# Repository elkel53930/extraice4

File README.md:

# ExtraICE4

ExtraICE4 is a competition robot called Micromouse.

For more information on Micromouse competitions, please see the [website](https://www.ntf.or.jp/) of the New Technology Foundation.

## Hardware

- 3DCAD data by Fusion360 : https://t.co/qPmjVBnEnc
  - STL file for 3D printing : under `mecha` directory
- Schematic and PCB design by KiCad7 : under `kicad/extraice` directory

## Firmware

The firmware is written by Rust language.

See [The Rust on ESP Book](https://esp-rs.github.io/book/) for instructions on how to set up the development environment.

The firmware is located under `fsw` directory. This directory is a sub-module, which is actually the micromouse-esp32 repository.

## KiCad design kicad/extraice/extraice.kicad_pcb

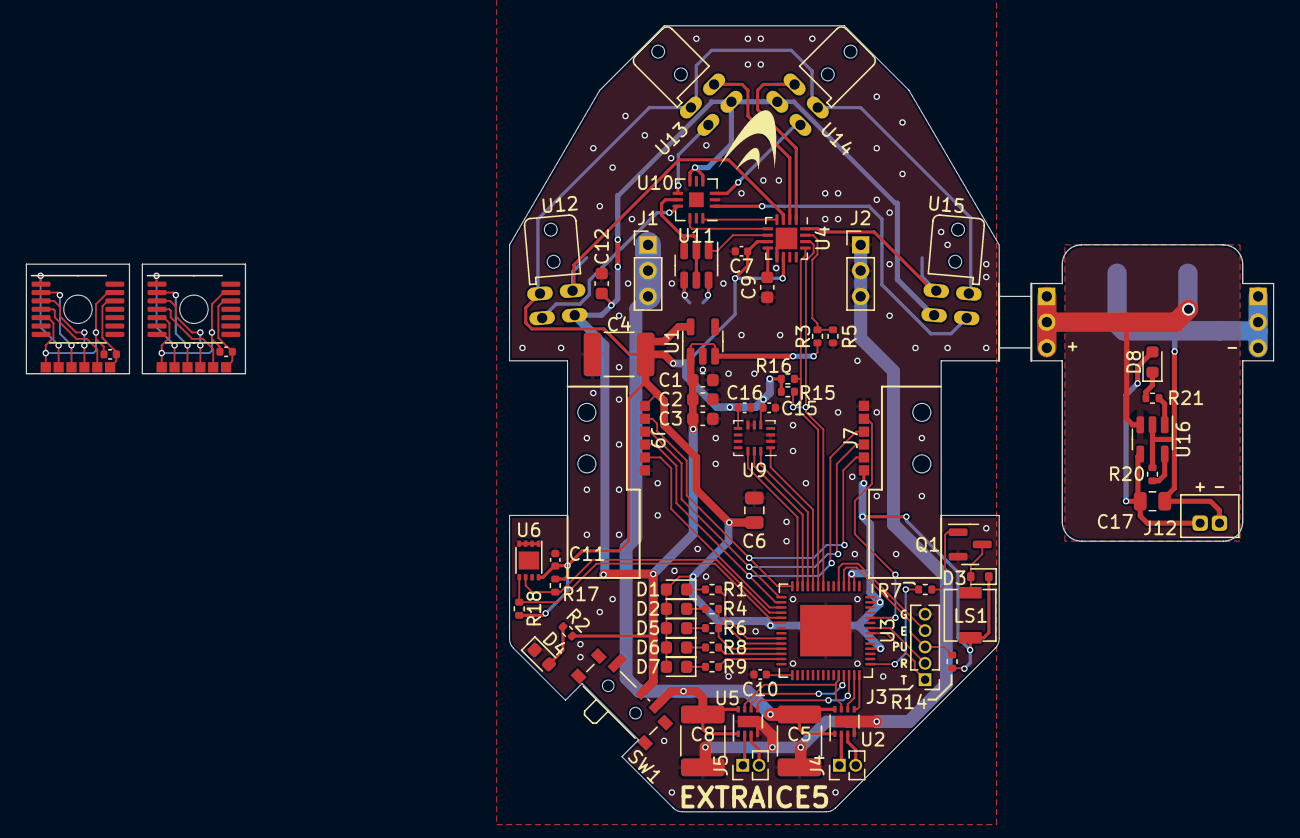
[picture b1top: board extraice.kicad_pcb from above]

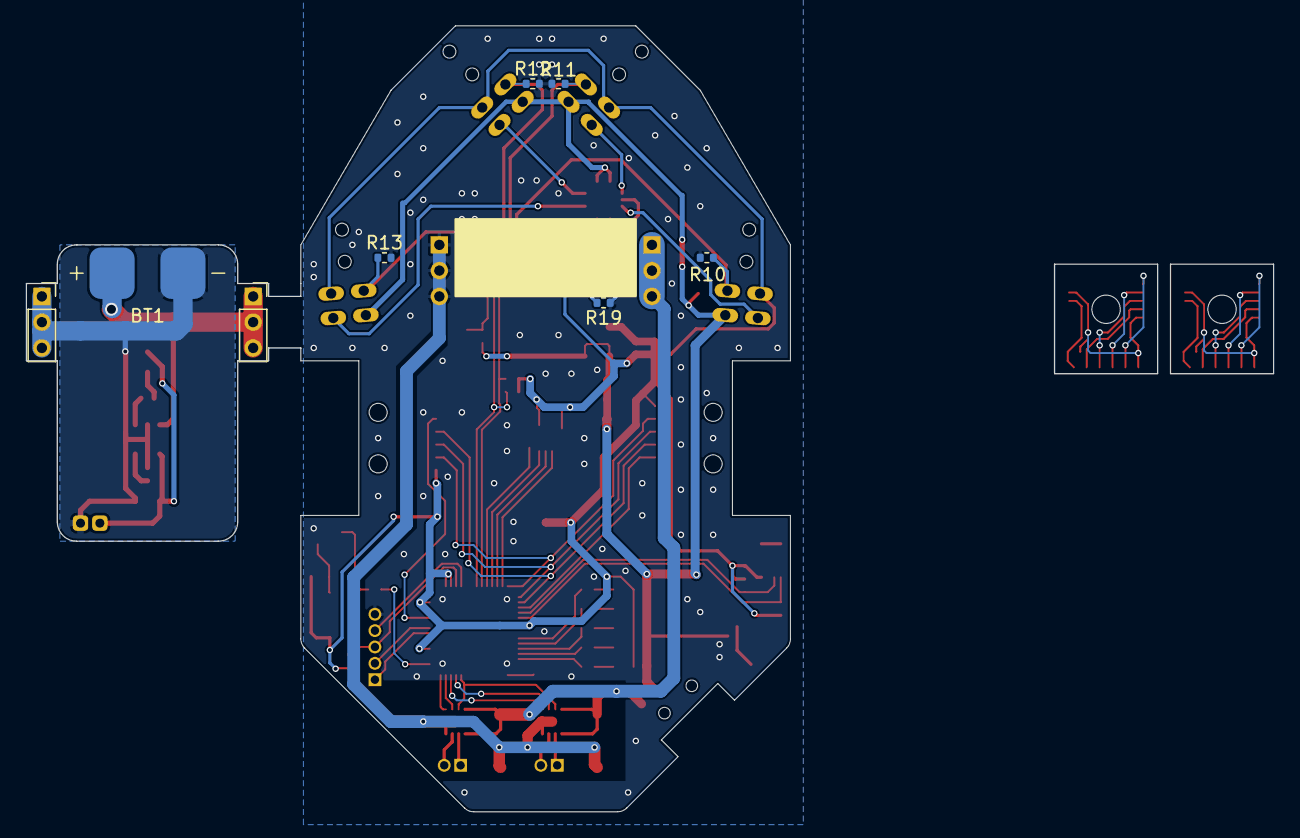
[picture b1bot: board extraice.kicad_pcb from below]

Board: 2 copper layers, 96.8 x 60.9 mm, 84 parts (8 on the bottom side), 78 nets.

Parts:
BT1: 100mAh LiPo; Battery
C1, C2, C3: 1608 10V 4.7uF; C_0603_1608Metric
C4, C5, C8: 4532 10u 16V; C_1812_4532Metric
C6, C17: 2012 35V 10uF; C_0805_2012Metric
C7, C10, C11, C13, C14, C15, C16: 1005 50V 0.1uF; C_0402_1005Metric
C9, C12: 1608 35V 1uF; C_0603_1608Metric
D1, D2, D5, D6, D7, D8: 1608 LED; LED_0603_1608Metric
D3: BAS516; D_SOD-523
D4: 1608 R LED; LED_0603_1608Metric
H1, H2, H3, H4: Φ1.4; Hole1.4
H5, H6: Φ2.2; MountingHole_2.2mm_M2
J1, J2: Conn_01x03; PinHeader_1x03_P2.00mm_Vertical
J3: Conn_01x05; PinHeader_1x05_P1.27mm_Vertical
J4, J5: Conn_01x02; PinHeader_1x02_P1.27mm_Vertical
J6, J8: EncSide; EncoderTerminal
J7, J9: MainSide; EncoderTerminal
J10, J11: Conn_01x03; PinSocket_1x03_P2.00mm_Vertical
J12: Conn_01x02; B2B-ZH
LS1: SMT-0440-T-2-R
Q1: MMBT3904; SOT-23
R1, R4, R6, R8, R9, R15, R16, R17, R18, R21: 1005 1k; R_0402_1005Metric
R2, R3, R5, R14, R20: 1005 10k; R_0402_1005Metric
R7, R10, R11, R12, R13: 1005 470 1%; R_0402_1005Metric
R19: 1005 6.2; R_0402_1005Metric
SW1: PCM12SMTR; SW_SPDT_PCM12
U1: XC6221B302GR; SOT-23-5
U2, U5: DRV8837C; WSON-8-1EP_2x2mm_P0.5mm_EP0.9x1.6mm
U3: ESP32-S3-PICO-1-N8R2; QFN-56-1EP_7x7mm_P0.4mm_EP4x4mm
U4: TLA2528IRTER; WQFN-16-1EP_3x3mm_P0.5mm_EP1.68x1.68mm
U6: MB85RC64TA; LCC-8P-M04
U7, U8: AS5047D; TSSOP-14_4.4x5mm_P0.65mm
U9: LSM6DSR; Bosch_LGA-14_3x2.5mm_P0.5mm
U10: DG2034EDN; QFN-12-1EP_3x3mm_P0.5_EP1.15x1.15
U11: BCR421; SOT-26
U12, U13: PhotoSensorL
U14, U15: PhotoSensorR
U16: LTC4054ES5-4.2; TSOT-23-5

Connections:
+3V0: C4.1, C6.1, C7.1, C11.1, C15.1, C16.1, D1.2 (A), D2.2 (A), D3.1 (K), D5.2 (A), D6.2 (A), D7.2 (A), J7.1, J9.1, LS1.1, R14.2, R15.2, R16.2, R17.2, R18.2, U1.5 (VOUT), U3.2 (VDD3P3), U3.3 (VDD3P3), U3.20 (VDD3P3_RTC), U3.46 (VDD3P3_CPU), U3.55 (VDDA), U3.56 (VDDA), U4.7 (AVDD), U4.10 (DVDD), U6.8 (VDD), U9.5 (Vdd_IO), U9.8 (Vdd), U12.2, U13.2, U14.2, U15.2
+BATT: C1.2, C2.2, C3.2, C12.1, R2.2, R3.2, SW1.2 (B), U1.1 (VIN), U1.3 (CE), U10.4 (EN), U10.6 (V+), U12.3, U13.3, U14.3, U15.3
/BATT_SEN: R3.1, R5.2, U4.15 (AIN0/GPIO0)
/BUZZ: R7.1, U3.43 (GPIO38)
/CHIP_PU: J3.3, R14.1, U3.4 (CHIP_PU)
/CS_ENC_L: J9.5, U3.17 (GPIO12)
/CS_ENC_R: J7.5, U3.52 (GPIO46)
/CS_IMU: U3.13 (GPIO8), U9.12 (CS)
/CWCCW_L: U3.40 (GPIO35), U5.5 (IN2)
/CWCCW_R: U2.5 (IN2), U3.42 (GPIO37)
/GPIO0: J3.4, U3.5 (GPIO0)
/LED_0: R1.2, U3.23 (GPIO17)
/LED_1: R4.2, U3.24 (GPIO18)
/LED_2: R6.2, U3.25 (GPIO19)
/LED_3: R8.2, U3.26 (GPIO20)
/LED_4: R9.2, U3.27 (GPIO21)
/LED_SEL0: U4.4 (AIN5/GPIO5), U10.12 (A0)
/LED_SEL1: U4.5 (AIN6/GPIO6), U10.10 (A1)
/MOT_SLEEP: U2.7 (~SLEEP), U3.38 (GPIO33), U5.7 (~SLEEP)
/PWM_L: U3.39 (GPIO34), U5.6 (IN1)
/PWM_R: U2.6 (IN1), U3.41 (GPIO36)
/RXD: J3.2, U3.50 (U0RXD)
/SCL0: R16.1, U3.9 (GPIO4), U4.13 (SCL)
/SCL1: R18.1, U3.19 (GPIO14), U6.5 (SDA)
/SDA0: R15.1, U3.8 (GPIO3), U4.14 (SDA)
/SDA1: R17.1, U3.18 (GPIO13), U6.6 (SCL)
/SEN_LED_ENA: U4.6 (AIN7/GPIO7), U11.1 (EN)
/SEN_LF: R10.1, U4.3 (AIN4/GPIO4), U12.1
/SEN_LS: R11.1, U4.2 (AIN3/GPIO3), U13.1
/SEN_RF: R13.1, U4.16 (AIN1/GPIO1), U15.1
/SEN_RS: R12.1, U4.1 (AIN2/GPIO2), U14.1
/SPI1_MISO: J7.3, J9.3, U3.15 (GPIO10)
/SPI1_MOSI: J7.2, J9.2, U3.14 (GPIO9)
/SPI1_SCK: J7.4, J9.4, U3.16 (GPIO11)
/SPI2_MISO: U3.10 (GPIO5), U9.1 (SDO/SA0)
/SPI2_MOSI: U3.11 (GPIO6), U9.14 (SDA)
/SPI2_SCK: U3.12 (GPIO7), U9.13 (SCL)
/TXD: J3.1, U3.49 (U0TXD)
/V_MOT: C5.1, C8.1, J1.1, J1.2, J1.3, SW1.3 (C), U2.1 (VM), U2.8 (VCC), U5.1 (VM), U5.8 (VCC)
GND: C1.1, C2.1, C3.1, C4.2, C5.2, C6.2, C7.2, C8.2, C9.1, C10.2, C11.2, C12.2, C15.2, C16.2, D4.1 (K), J2.1, J2.2, J2.3, J3.5, J7.6, J9.6, Q1.2 (E), R5.1, R10.2, R11.2, R12.2, R13.2, R19.1, U1.2 (GND), U2.4 (GND), U2.9 (GND), U3.57 (GND), U4.9 (GND), U4.17 (THPD), U5.4 (GND), U5.9 (GND), U6.1 (A0), U6.2 (A1), U6.3 (A2), U6.4 (VSS), U9.2 (SDx), U9.3 (SCx), U9.6 (GND), U9.7 (GND), U10.2 (GND), U11.4 (GND)
unnamed: BT1.1 (+), J10.1, J10.2, J10.3, U16.3 (BAT)
unnamed: BT1.2 (-), C17.2, J11.1, J11.2, J11.3, J12.1, R20.1, U16.2 (GND)
unnamed: D1.1 (K), R1.1
unnamed: D2.1 (K), R4.1
unnamed: D3.2 (A), LS1.2, Q1.3 (C)
unnamed: D4.2 (A), R2.1
unnamed: D5.1 (K), R6.1
unnamed: D6.1 (K), R8.1
unnamed: D7.1 (K), R9.1
unnamed: C17.1, D8.2 (A), J12.2, U16.4 (V_{CC})
unnamed: D8.1 (K), R21.2
unnamed: J4.1, U2.2 (OUT1)
unnamed: J4.2, U2.3 (OUT2)
unnamed: J5.1, U5.2 (OUT1)
unnamed: J5.2, U5.3 (OUT2)
unnamed: C13.1, J6.1, U7.12 (VDD3V3)
unnamed: J6.2, U7.4 (MOSI)
unnamed: J6.3, U7.3 (MISO)
unnamed: J6.4, U7.2 (CLK)
unnamed: J6.5, U7.1 (~CS)
unnamed: C13.2, J6.6, U7.5 (TST), U7.13 (GND)
unnamed: C14.1, J8.1, U8.12 (VDD3V3)
unnamed: J8.2, U8.4 (MOSI)
unnamed: J8.3, U8.3 (MISO)
unnamed: J8.4, U8.2 (CLK)
unnamed: J8.5, U8.1 (~CS)
unnamed: C14.2, J8.6, U8.5 (TST), U8.13 (GND)
unnamed: Q1.1 (B), R7.2
unnamed: C10.1, U3.29 (VDD_SPI)
unnamed: C9.2, U4.8 (DECAP)
unnamed: U10.8 (COM), U11.2 (OUT), U11.3 (OUT), U11.5 (OUT)
unnamed: U10.1 (S1), U15.4
unnamed: U10.9 (S2), U12.4
unnamed: U10.3 (S3), U14.4
unnamed: U10.7 (S4), U13.4
unnamed: R19.2, U11.6 (Rext)
unnamed: R20.2, U16.5 (PROG)
unnamed: R21.1, U16.1 (~CHRG)

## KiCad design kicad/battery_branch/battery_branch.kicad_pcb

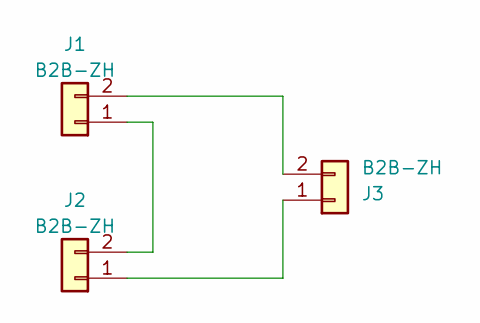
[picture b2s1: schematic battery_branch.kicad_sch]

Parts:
J1, J2, J3: B2B-ZH

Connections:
unnamed: J1.1, J2.2
unnamed: J1.2, J3.2
unnamed: J2.1, J3.1

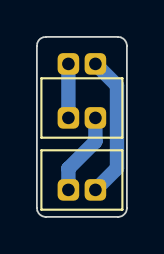
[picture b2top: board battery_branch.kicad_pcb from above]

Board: 2 copper layers, 5.0 x 10.0 mm, 3 parts (1 on the bottom side), 3 nets.

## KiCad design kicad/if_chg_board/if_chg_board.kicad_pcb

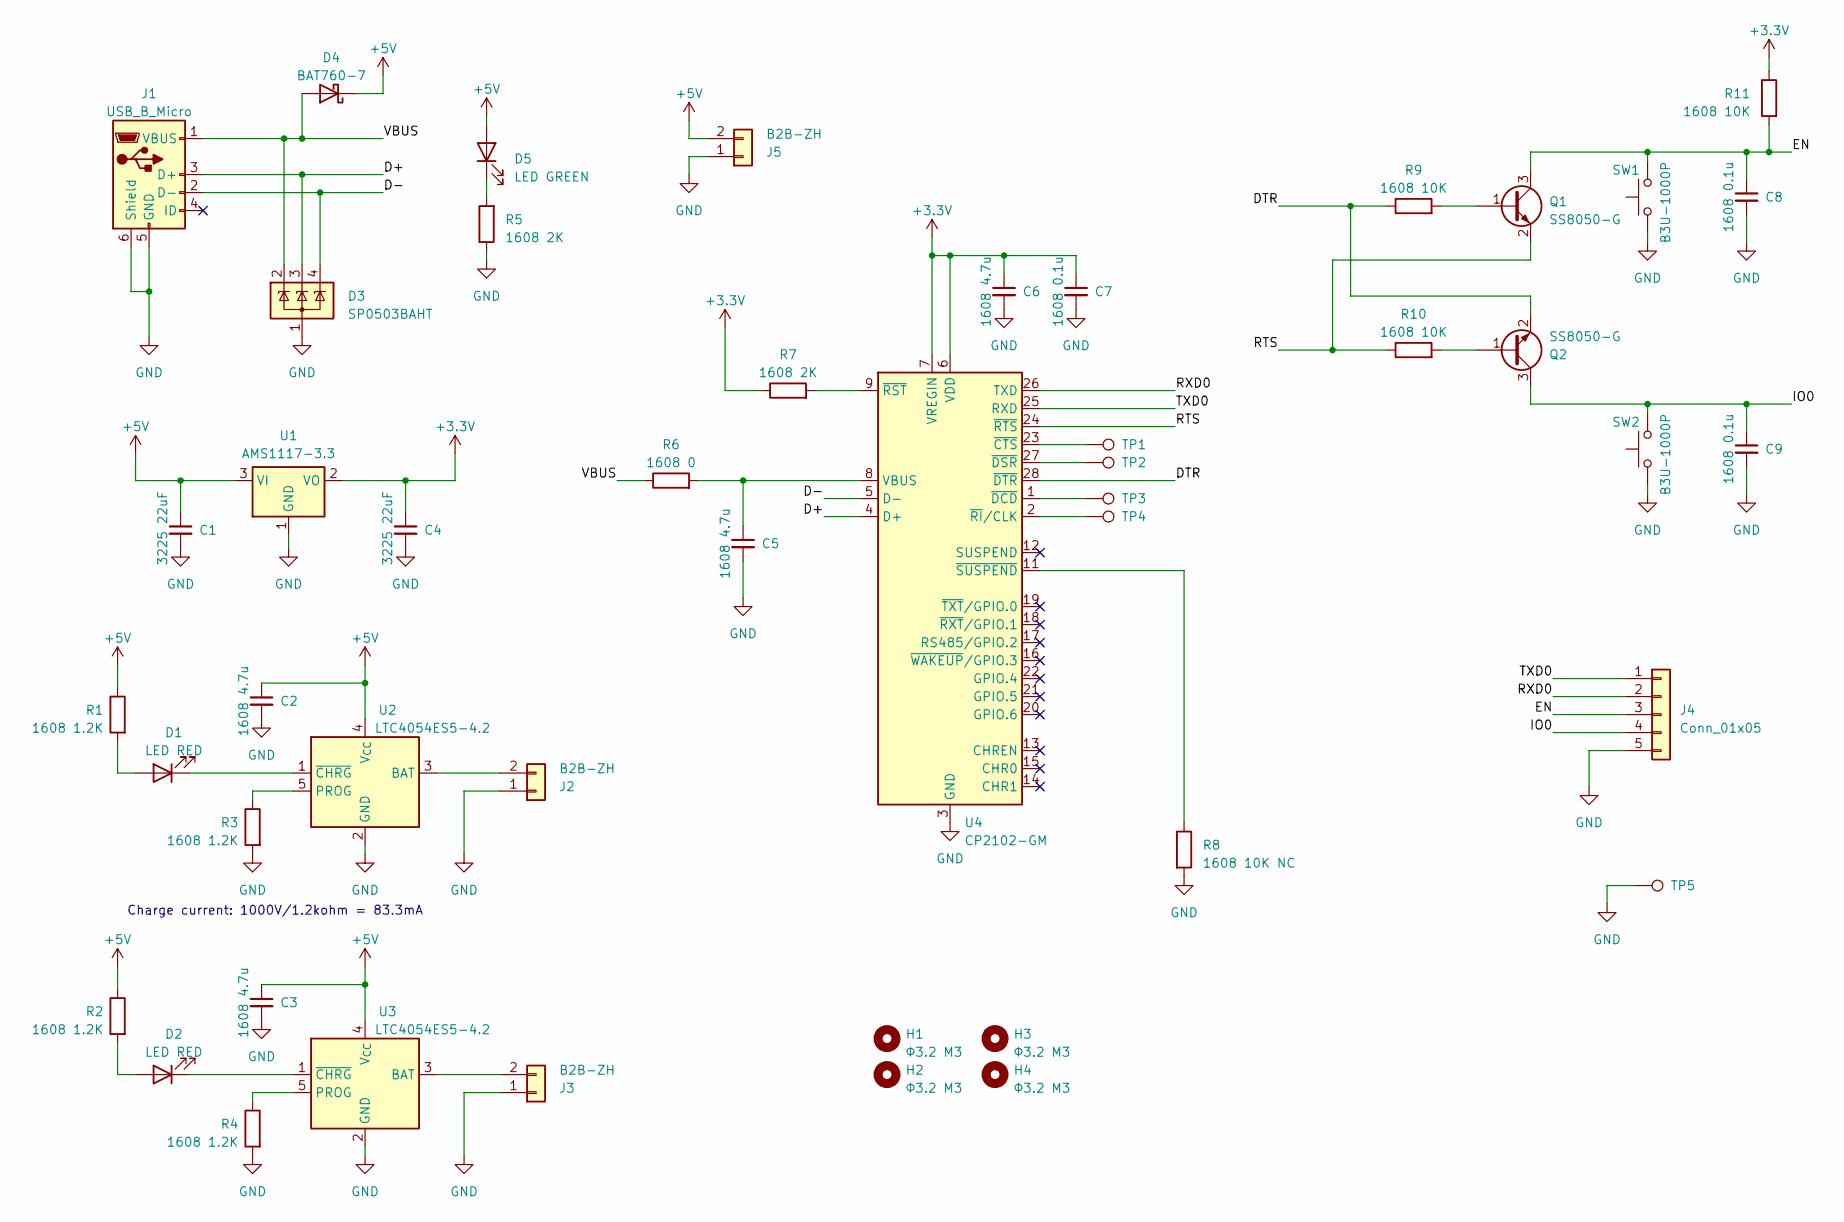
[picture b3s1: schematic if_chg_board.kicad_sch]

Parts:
C1, C4: 3225 22uF; C_1210_3225Metric
C2, C3, C5, C6: 1608 4.7u; C_0603_1608Metric
C7, C8, C9: 1608 0.1u; C_0603_1608Metric
D1, D2: LED RED; LED_0603_1608Metric
D3: SP0503BAHT; SOT-143
D4: BAT760-7; D_SOD-323
D5: LED GREEN; LED_0603_1608Metric
H1, H2, H3, H4: Φ3.2 M3; MountingHole_3.2mm_M3
J1: USB_B_Micro; USB_Micro-B_Molex-105017-0001
J2, J3: B2B-ZH
J4: Conn_01x05; PinHeader_1x05_P1.27mm_Vertical
J5: B2B-ZH; PinHeader_1x02_P2.54mm_Vertical
Q1, Q2: SS8050-G; SOT-23
R1, R2, R3, R4: 1608 1.2K; R_0603_1608Metric
R5, R7: 1608 2K; R_0603_1608Metric
R6: 1608 0; R_0603_1608Metric
R8: 1608 10K NC; R_0603_1608Metric
R9, R10, R11: 1608 10K; R_0603_1608Metric
SW1, SW2: B3U-1000P; SW_SPST_B3U-1000P
TP1, TP2, TP3, TP4: TestPoint_Pad_D1.5mm
TP5: PinHeader_1x01_P2.54mm_Vertical
U1: AMS1117-3.3; SOT-223-3_TabPin2
U2, U3: LTC4054ES5-4.2; TSOT-23-5
U4: CP2102-GM; QFN-28-1EP_5x5mm_P0.5mm_EP3.35x3.35mm

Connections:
+3.3V: C4.1, C6.1, C7.1, R7.1, R11.1, U1.2 (VO), U4.6 (VDD), U4.7 (VREGIN)
+5V: C1.1, C2.1, C3.1, D4.1 (K), D5.2 (A), J5.2, R1.1, R2.1, U1.3 (VI), U2.4 (V_{CC}), U3.4 (V_{CC})
/D+: D3.3 (K), J1.3 (D+), U4.4 (D+)
/D-: D3.4 (K), J1.2 (D-), U4.5 (D-)
/DTR: Q2.2 (E), R9.1, U4.28 (~DTR)
/EN: C8.1, J4.3, Q1.3 (C), R11.2, SW1.2
/IO0: C9.1, J4.4, Q2.3 (C), SW2.2
/RTS: Q1.2 (E), R10.1, U4.24 (~RTS)
/RXD0: J4.2, U4.26 (TXD)
/TXD0: J4.1, U4.25 (RXD)
/VBUS: D3.2 (K), D4.2 (A), J1.1 (VBUS), R6.1
GND: C1.2, C2.2, C3.2, C4.2, C5.2, C6.2, C7.2, C8.2, C9.2, D3.1 (A), J1.5 (GND), J1.6 (Shield), J2.1, J3.1, J4.5, J5.1, R3.2, R4.2, R5.1, R8.2, SW1.1, SW2.1, TP5.1, U1.1 (GND), U2.2 (GND), U3.2 (GND), U4.3 (GND), U4.29 (GND)
unnamed: D1.2 (A), R1.2
unnamed: D1.1 (K), U2.1 (~CHRG)
unnamed: D2.2 (A), R2.2
unnamed: D2.1 (K), U3.1 (~CHRG)
unnamed: D5.1 (K), R5.2
unnamed: J2.2, U2.3 (BAT)
unnamed: J3.2, U3.3 (BAT)
unnamed: Q1.1 (B), R9.2
unnamed: Q2.1 (B), R10.2
unnamed: R3.1, U2.5 (PROG)
unnamed: R4.1, U3.5 (PROG)
unnamed: C5.1, R6.2, U4.8 (VBUS)
unnamed: TP1.1, U4.23 (~CTS)
unnamed: TP3.1, U4.1 (~DCD)
unnamed: TP2.1, U4.27 (~DSR)
unnamed: TP4.1, U4.2 (~RI/CLK)
unnamed: R7.2, U4.9 (~RST)
unnamed: R8.1, U4.11 (~SUSPEND)

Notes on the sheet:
Charge current: 1000V/1.2kohm = 83.3mA

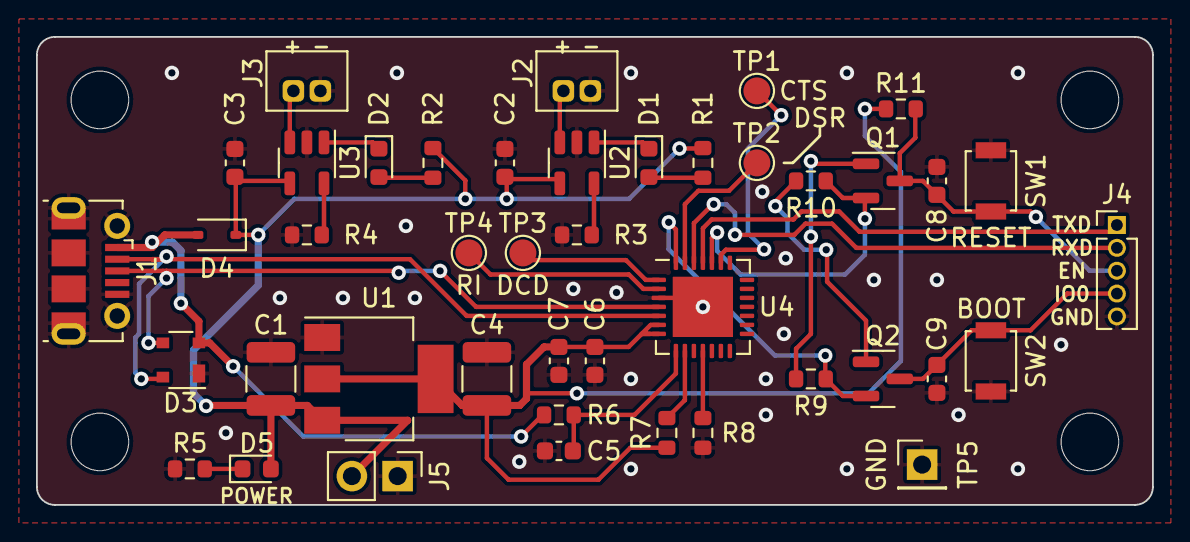
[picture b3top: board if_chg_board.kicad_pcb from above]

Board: 2 copper layers, 62.0 x 26.0 mm, 47 parts (0 on the bottom side), 30 nets.

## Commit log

2023-06-17 Add mechanical parts to be output by 3D printer
2023-06-17 Add firmware repo as a submodule.
2023-06-21 add README.md
2023-07-07 Fix problems identified during implementation
    - ESP32 supports only crystal oscillator, not resonator.
    - The package and capacitance of capacitor C1 were incorrect.
    - Fix a ESP32 pin name. GPIO15 -> GPIO14.
2023-07-20 Interface & charning board
2023-07-20 Update if_chg_board
2023-07-20 Add battery branch board
2023-07-20 Add .gitignore for KiCad (from https://github.com/github/gitignore/blob/main/KiCad.gitignore)
2023-07-21 Add parts list for if_chg_board
2023-11-15 Fix battery charge current
2023-11-18 Remove unnecessary wiring
2023-11-18 Add a pull-up register to the CHIP-PU pin.
2023-11-21 Remove fsw
2024-02-25 Artwork for 4A completed
    Need to check details.
2024-02-27 Change some GPIO assignments
2024-07-11 EXTRAICE5
